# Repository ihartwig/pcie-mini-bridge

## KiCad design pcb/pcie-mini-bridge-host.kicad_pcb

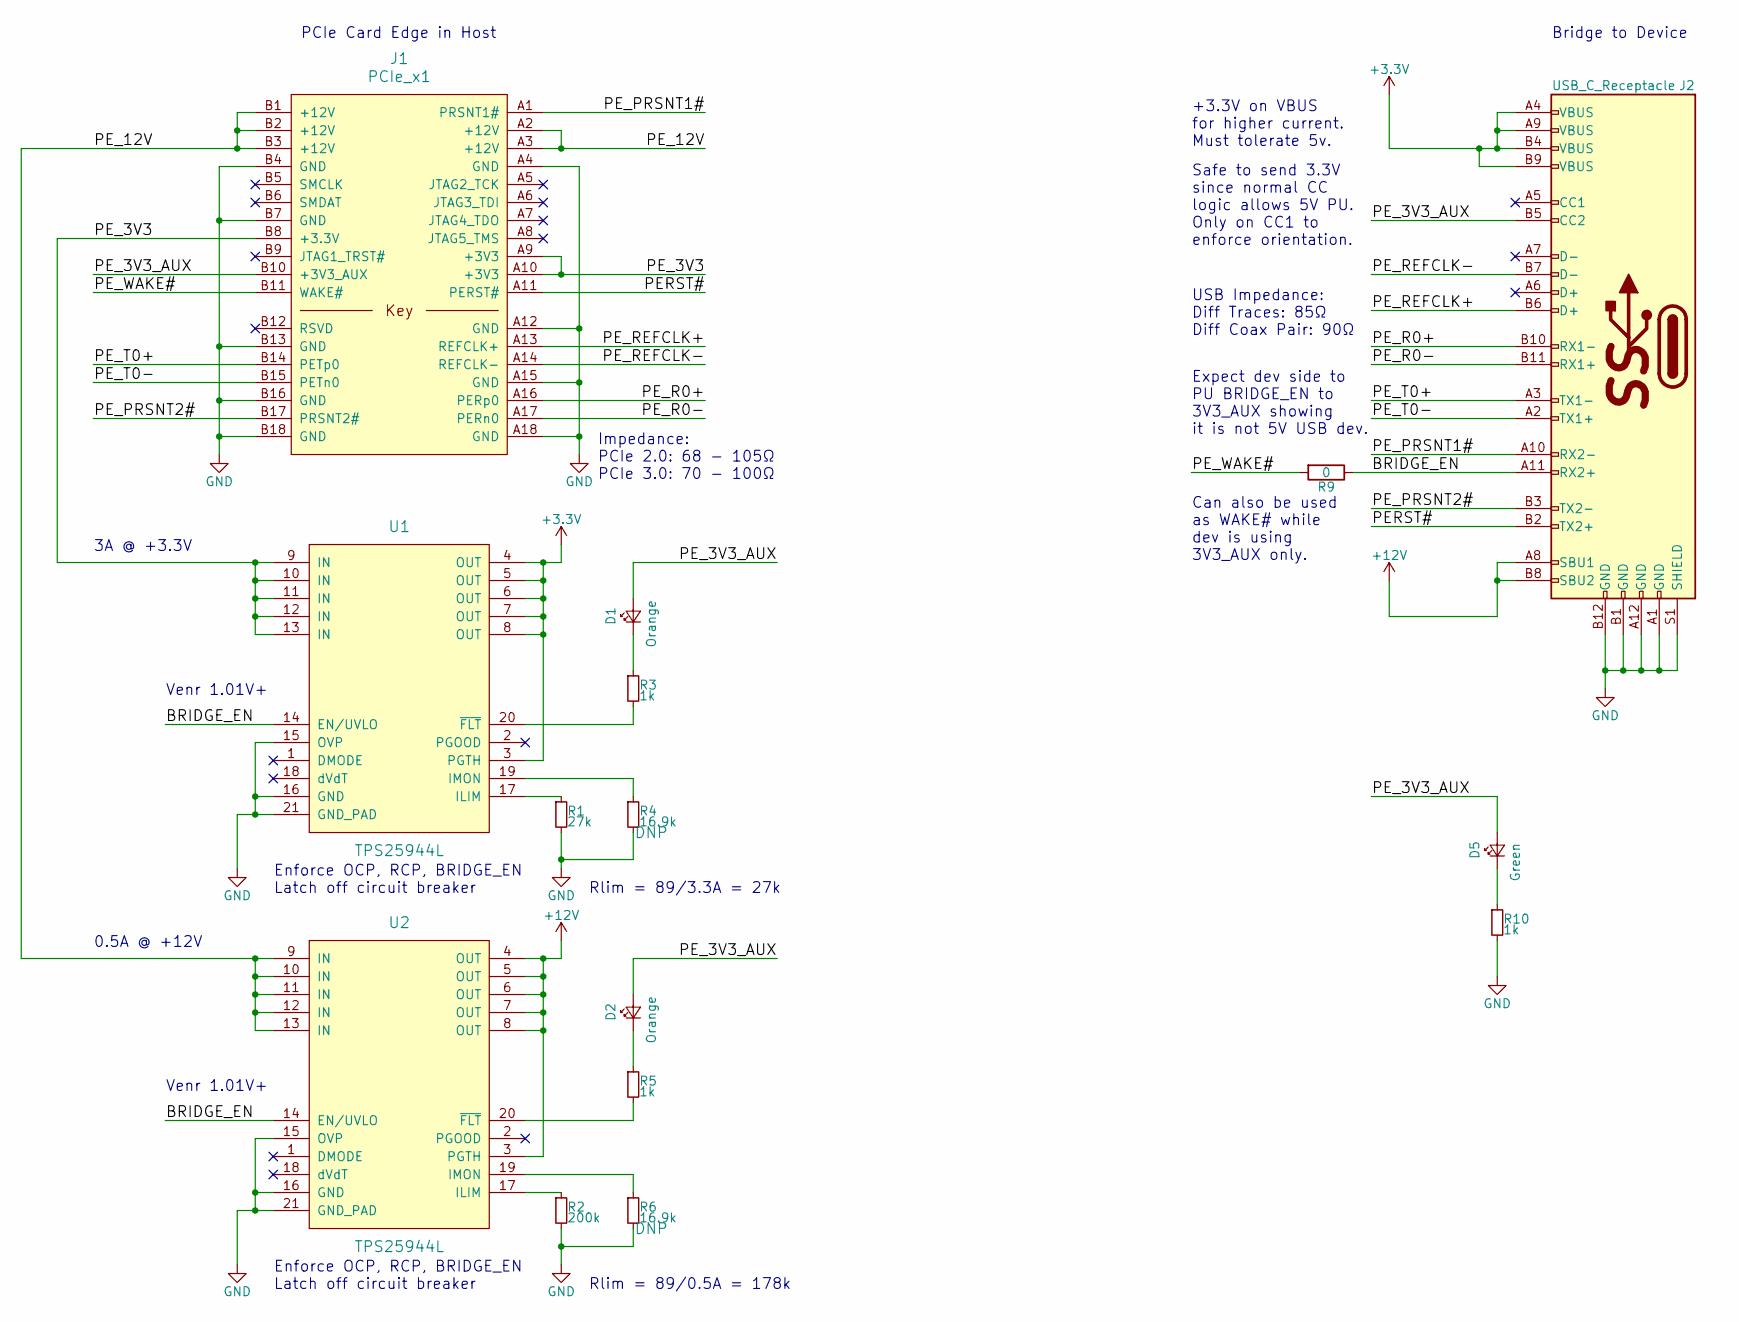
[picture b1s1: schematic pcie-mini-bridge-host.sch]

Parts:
D1, D2: Orange; LED_0603; Mfg Part No LTST-C190KFKT; Digikey Part No 160-1434-1-ND
D5: Green; LED_0603; Mfg Part No LTST-C190GKT; Digikey Part No 160-1183-1-ND
J1: PCIe_x1; PCIe_Fingers_x1
J2: USB_C_Receptacle; USB_C_Receptacle_Amphenol_12401610E4-2A; Mfg PN 12401548E4#2A; Digikey PN 12401548E4#2ACT-ND
R1: 27k; R_0603
R2: 200k; R_0603
R3, R5, R10: 1k; R_0603
R4, R6: 16.9k; R_0603
R9: 0; R_0603
U1, U2: TPS25944L; QFN-20-1EP_3x4mm_Pitch0.5mm; Mfg Part No TPS25944LRVCR; Digikey Part No 296-42152-1-ND

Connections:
+3V3: J2.A4 (VBUS), J2.A9 (VBUS), J2.B4 (VBUS), J2.B9 (VBUS), U1.3 (PGTH), U1.4 (OUT), U1.5 (OUT), U1.6 (OUT), U1.7 (OUT), U1.8 (OUT)
+12V: J2.A8 (SBU1), J2.B8 (SBU2), U2.3 (PGTH), U2.4 (OUT), U2.5 (OUT), U2.6 (OUT), U2.7 (OUT), U2.8 (OUT)
/BRIDGE_EN: J2.A11 (RX2+), R9.1, U1.14 (EN/UVLO), U2.14 (EN/UVLO)
/PERST#: J1.A11 (PERST#), J2.B2 (TX2+)
/PE_3V3: J1.A9 (+3V3), J1.A10 (+3V3), J1.B8 (+3.3V), U1.9 (IN), U1.10 (IN), U1.11 (IN), U1.12 (IN), U1.13 (IN)
/PE_3V3_AUX: D1.2 (A), D2.2 (A), D5.2 (A), J1.B10 (+3V3_AUX), J2.B5 (CC2)
/PE_12V: J1.A2 (+12V), J1.A3 (+12V), J1.B1 (+12V), J1.B2 (+12V), J1.B3 (+12V), U2.9 (IN), U2.10 (IN), U2.11 (IN), U2.12 (IN), U2.13 (IN)
/PE_PRSNT1#: J1.A1 (PRSNT1#), J2.A10 (RX2-)
/PE_PRSNT2#: J1.B17 (PRSNT2#), J2.B3 (TX2-)
/PE_R0+: J1.A16 (PERp0), J2.B10 (RX1-)
/PE_R0-: J1.A17 (PERn0), J2.B11 (RX1+)
/PE_REFCLK+: J1.A13 (REFCLK+), J2.B6 (D+)
/PE_REFCLK-: J1.A14 (REFCLK-), J2.B7 (D-)
/PE_T0+: J1.B14 (PETp0), J2.A3 (TX1-)
/PE_T0-: J1.B15 (PETn0), J2.A2 (TX1+)
/PE_WAKE#: J1.B11 (WAKE#), R9.2
GND: J1.A4 (GND), J1.A12 (GND), J1.A15 (GND), J1.A18 (GND), J1.B4 (GND), J1.B7 (GND), J1.B13 (GND), J1.B16 (GND), J1.B18 (GND), J2.A1 (GND), J2.A12 (GND), J2.B1 (GND), J2.B12 (GND), J2.S1 (SHIELD), R1.2, R2.2, R4.2, R6.2, R10.2, U1.15 (OVP), U1.16 (GND), U1.21 (GND_PAD), U2.15 (OVP), U2.16 (GND), U2.21 (GND_PAD)
unnamed: D1.1 (K), R3.1
unnamed: D2.1 (K), R5.1
unnamed: D5.1 (K), R10.1
unnamed: R1.1, U1.17 (ILIM)
unnamed: R2.1, U2.17 (ILIM)
unnamed: R3.2, U1.20 (~FLT)
unnamed: R4.1, U1.19 (IMON)
unnamed: R5.2, U2.20 (~FLT)
unnamed: R6.1, U2.19 (IMON)

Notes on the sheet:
Safe to send 3.3V since normal CC logic allows 5V PU. Only on CC1 to enforce orientation.
Expect dev side to PU BRIDGE_EN to 3V3_AUX showing it is not 5V USB dev.
Can also be used as WAKE# while dev is using 3V3_AUX only.
PCIe Card Edge in Host
Bridge to Device
0.5A @ +12V
3A @ +3.3V
+3.3V on VBUS for higher current. Must tolerate 5v.
Venr 1.01V+
Enforce OCP, RCP, BRIDGE_EN Latch off circuit breaker
Impedance: PCIe 2.0: 68 - 105Ω PCIe 3.0: 70 - 100Ω
Rlim = 89/3.3A = 27k
Rlim = 89/0.5A = 178k
USB Impedance: Diff Traces: 85Ω Diff Coax Pair: 90Ω

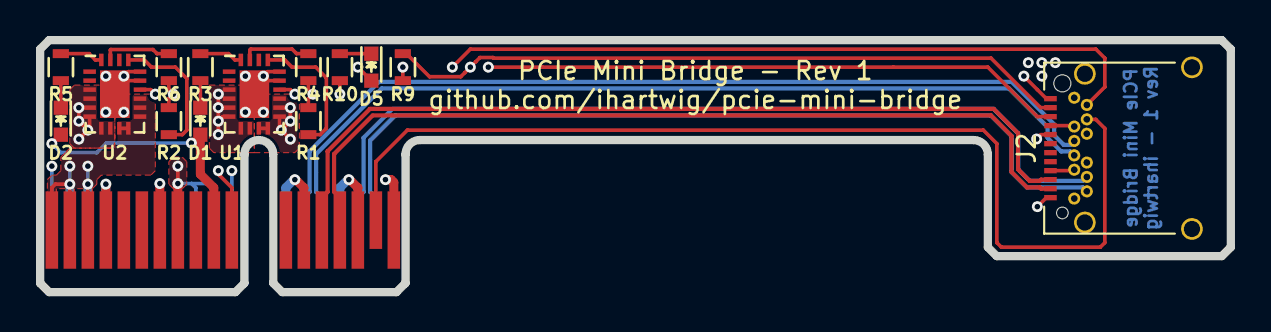
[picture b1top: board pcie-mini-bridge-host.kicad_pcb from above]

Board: 4 copper layers, 66.2 x 14.0 mm, 15 parts (0 on the bottom side), 26 nets.

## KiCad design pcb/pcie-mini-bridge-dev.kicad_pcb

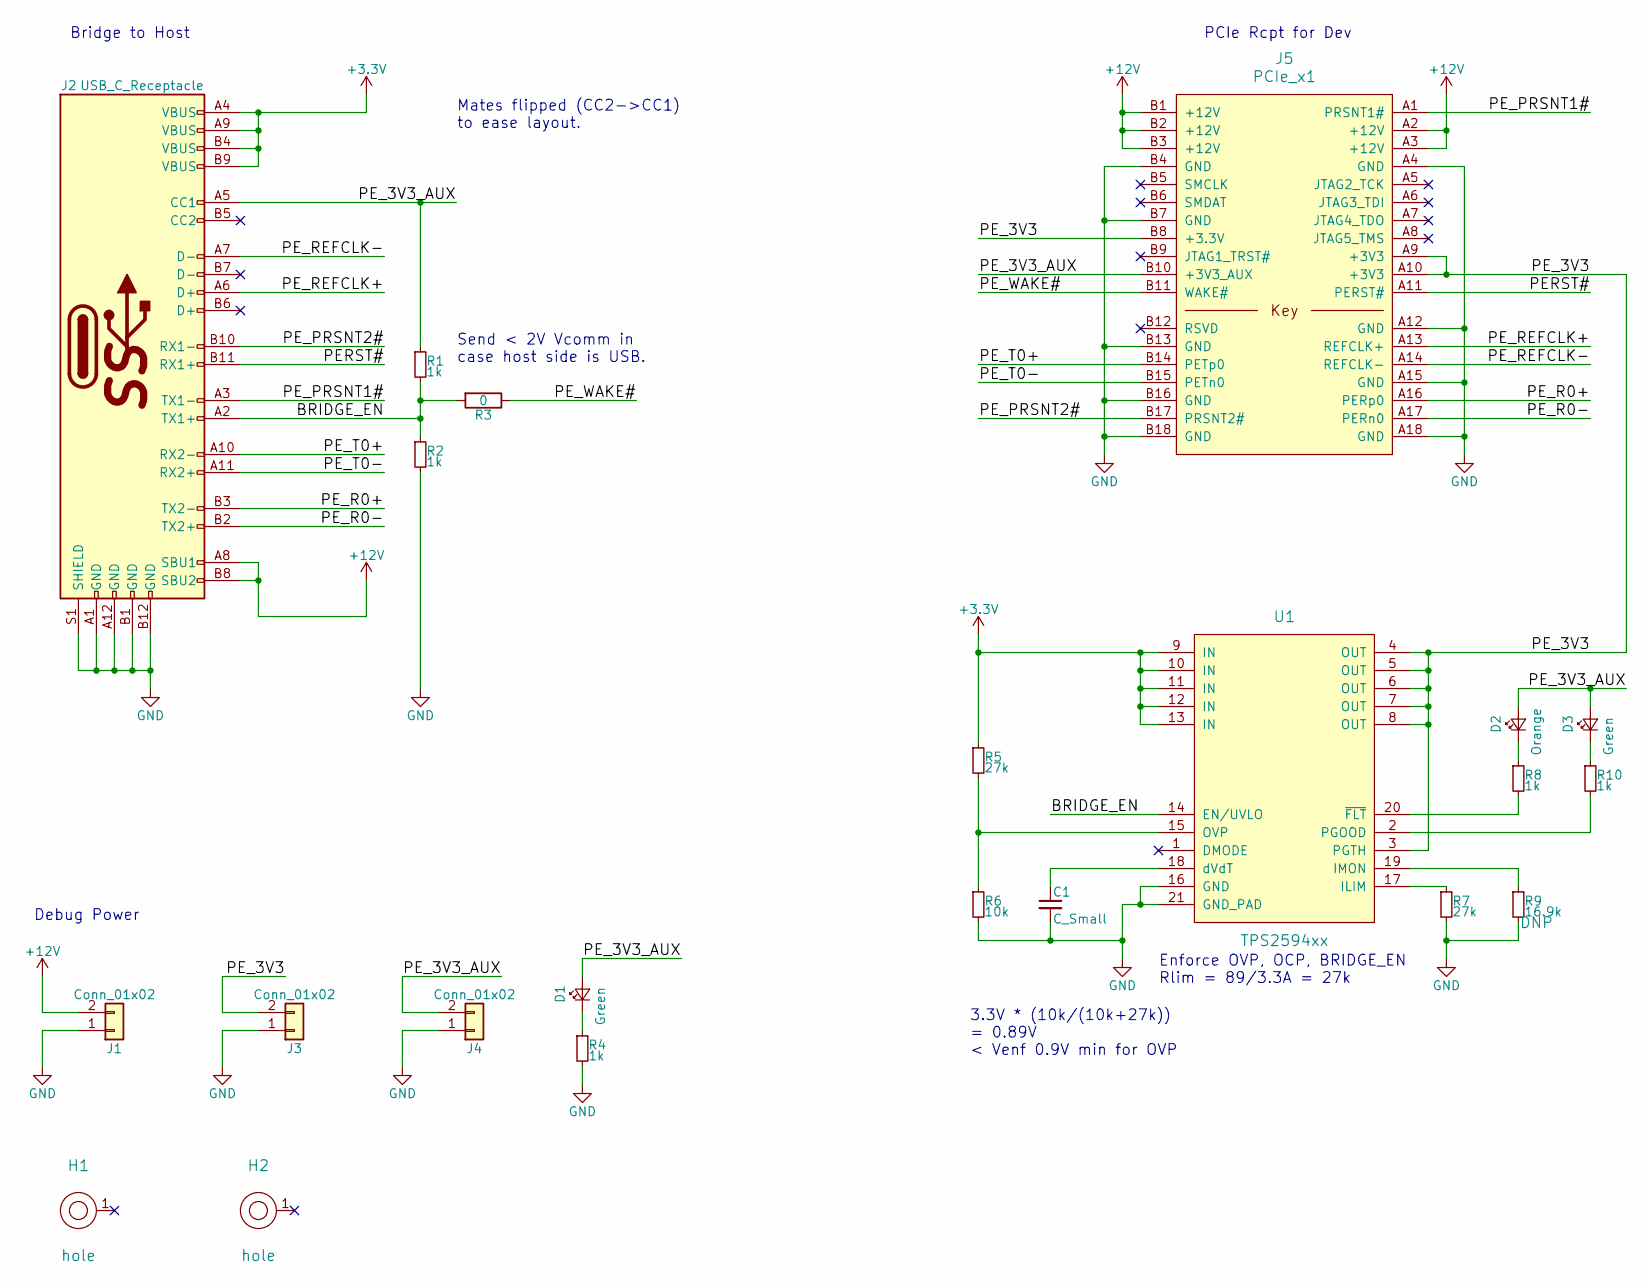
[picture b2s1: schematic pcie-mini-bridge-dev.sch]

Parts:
C1: C_Small; C_0603
D1, D3: Green; LED_0603; Mfg Part No LTST-C190GKT; Digikey Part No 160-1183-1-ND
D2: Orange; LED_0603; Mfg Part No LTST-C190KFKT; Digikey Part No 160-1434-1-ND
H1, H2: hole; hole-m3
J1, J3, J4: Conn_01x02; Pin_Header_Straight_1x02
J2: USB_C_Receptacle; USB_C_Receptacle_Amphenol_12401610E4-2A; Mfg PN 12401548E4#2A; Digikey PN 12401548E4#2ACT-ND
J5: PCIe_x1; PCIe_SMDEdge-NoPaste_TE_5-1734857-x; Mfg PN 5-1734857-5; Digikey PN A115312-ND
R1, R2, R4, R8, R10: 1k; R_0603
R3: 0; R_0603
R5, R7: 27k; R_0603
R6: 10k; R_0603
R9: 16.9k; R_0603
U1: TPS2594xx; QFN-20-1EP_3x4mm_Pitch0.5mm; Mfg Part No TPS25944LRVCR; Digikey Part No 296-42152-1-ND

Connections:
+3V3: J2.A4 (VBUS), J2.A9 (VBUS), J2.B4 (VBUS), J2.B9 (VBUS), R5.1, U1.9 (IN), U1.10 (IN), U1.11 (IN), U1.12 (IN), U1.13 (IN)
+12V: J1.2, J2.A8 (SBU1), J2.B8 (SBU2), J5.A2 (+12V), J5.A3 (+12V), J5.B1 (+12V), J5.B2 (+12V), J5.B3 (+12V)
/BRIDGE_EN: J2.A2 (TX1+), R1.2, R2.1, R3.2, U1.14 (EN/UVLO)
/PERST#: J2.B11 (RX1+), J5.A11 (PERST#)
/PE_3V3: J3.2, J5.A9 (+3V3), J5.A10 (+3V3), J5.B8 (+3.3V), U1.3 (PGTH), U1.4 (OUT), U1.5 (OUT), U1.6 (OUT), U1.7 (OUT), U1.8 (OUT)
/PE_3V3_AUX: D1.2 (A), D2.2 (A), D3.2 (A), J2.A5 (CC1), J4.2, J5.B10 (+3V3_AUX), R1.1
/PE_PRSNT1#: J2.A3 (TX1-), J5.A1 (PRSNT1#)
/PE_PRSNT2#: J2.B10 (RX1-), J5.B17 (PRSNT2#)
/PE_R0+: J2.B3 (TX2-), J5.A16 (PERp0)
/PE_R0-: J2.B2 (TX2+), J5.A17 (PERn0)
/PE_REFCLK+: J2.A6 (D+), J5.A13 (REFCLK+)
/PE_REFCLK-: J2.A7 (D-), J5.A14 (REFCLK-)
/PE_T0+: J2.A10 (RX2-), J5.B14 (PETp0)
/PE_T0-: J2.A11 (RX2+), J5.B15 (PETn0)
/PE_WAKE#: J5.B11 (WAKE#), R3.1
GND: C1.2, J1.1, J2.A1 (GND), J2.A12 (GND), J2.B1 (GND), J2.B12 (GND), J2.S1 (SHIELD), J3.1, J4.1, J5.A4 (GND), J5.A12 (GND), J5.A15 (GND), J5.A18 (GND), J5.B4 (GND), J5.B7 (GND), J5.B13 (GND), J5.B16 (GND), J5.B18 (GND), R2.2, R4.2, R6.2, R7.2, R9.2, U1.16 (GND), U1.21 (GND_PAD)
unnamed: C1.1, U1.18 (dVdT)
unnamed: D1.1 (K), R4.1
unnamed: D2.1 (K), R8.1
unnamed: D3.1 (K), R10.1
unnamed: R5.2, R6.1, U1.15 (OVP)
unnamed: R7.1, U1.17 (ILIM)
unnamed: R8.2, U1.20 (~FLT)
unnamed: R9.1, U1.19 (IMON)
unnamed: R10.2, U1.2 (PGOOD)

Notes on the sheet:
Send < 2V Vcomm in case host side is USB.
PCIe Rcpt for Dev
Bridge to Host
3.3V * (10k/(10k+27k)) = 0.89V < Venf 0.9V min for OVP
Enforce OVP, OCP, BRIDGE_EN Rlim = 89/3.3A = 27k
Debug Power
Mates flipped (CC2->CC1) to ease layout.

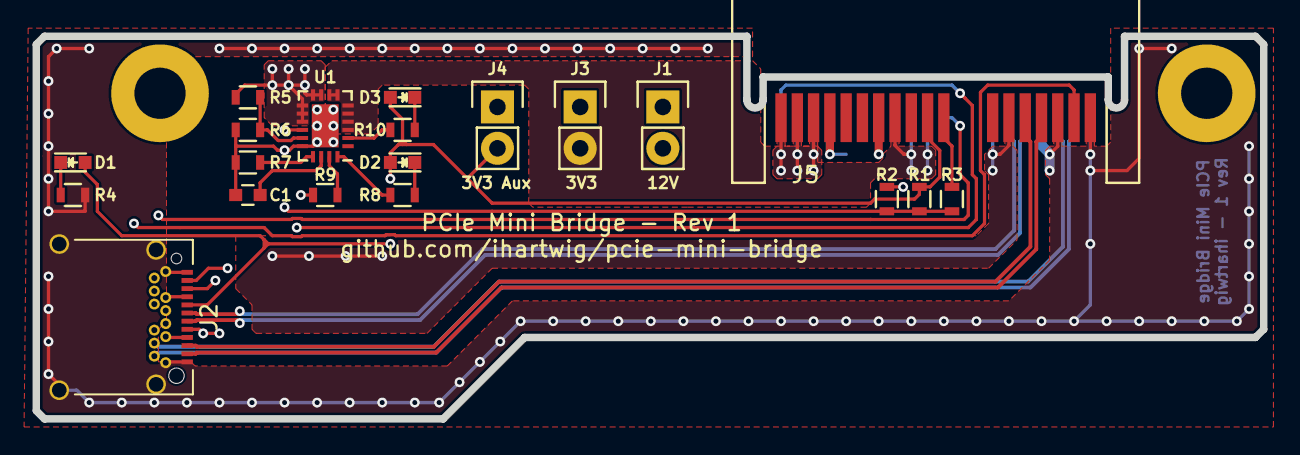
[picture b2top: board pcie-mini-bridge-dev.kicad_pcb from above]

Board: 4 copper layers, 75.4 x 23.5 mm, 22 parts (0 on the bottom side), 25 nets.

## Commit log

2017-11-24 Add LICENSE
2017-12-03 docs, schematic, footprints, host pcb layout
2017-12-19 dev pcb layout, outline and hole parts
2017-12-20 fix drc and dfm problems and make rev 1 gerbers
    * fix usb c recp. drc. change suggested .7/.4mm th/drills to .6728/.368mm th/drills to meet 6mil annular rings and 5mil spacing. remove slots.
    * clean up silk, add board labels
    * fix soldermask sizing to .051mm clearance with .077mm min width
    * remove PCIe length matching on host board because host + dev is correct length
2018-01-18 fix pcie footprints and remove paste and update gerbers
    * fix PCIe_Fingers and PCIe_SMDEdge had bottom cu with top mask/paste
    * make and use PCIe_SMDEdge-NoPaste_TE_5-1734857-x
2018-07-22 add schematic PDFs
